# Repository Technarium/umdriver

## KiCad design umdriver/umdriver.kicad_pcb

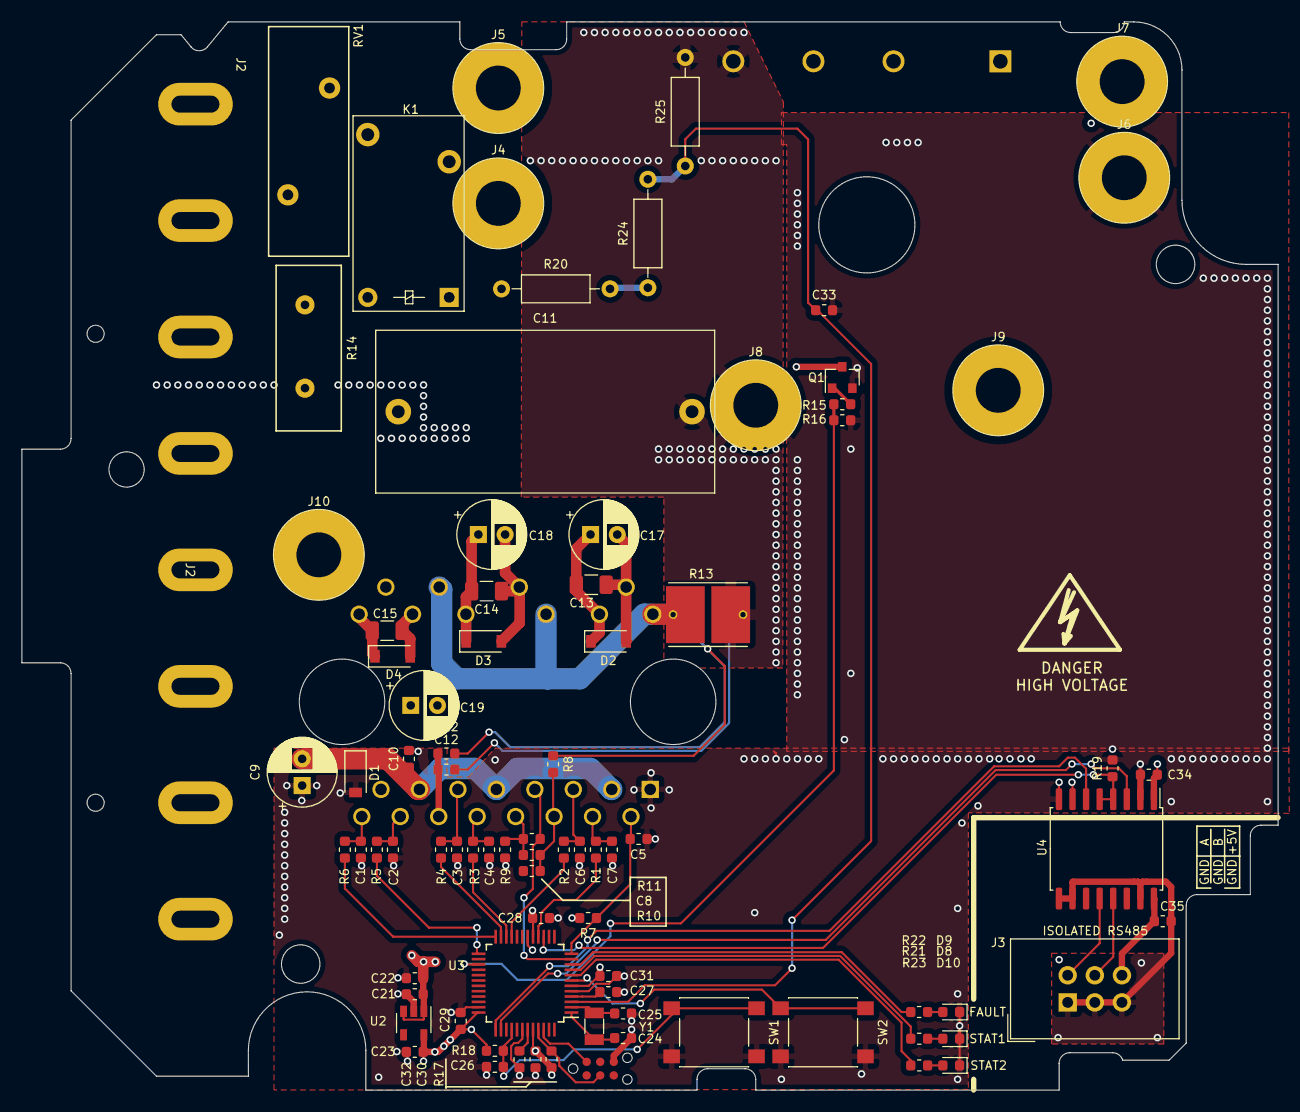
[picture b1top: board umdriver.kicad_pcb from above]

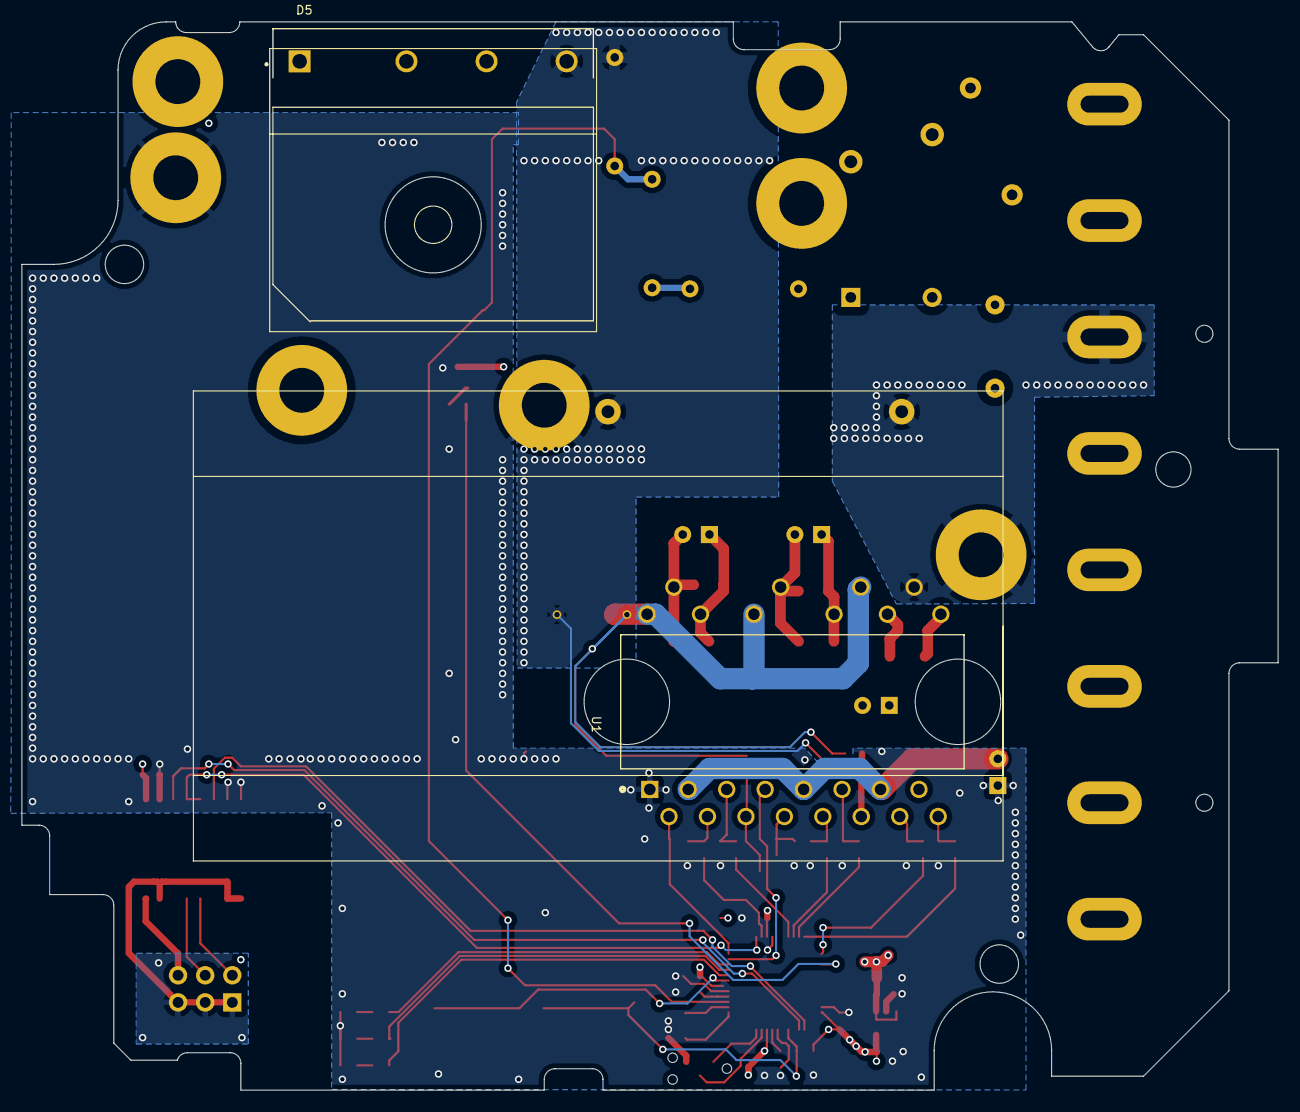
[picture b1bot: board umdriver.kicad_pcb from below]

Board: 4 copper layers, 117.6 x 100.0 mm, 87 parts (2 on the bottom side), 57 nets.

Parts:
C1, C2, C3, C4, C5, C6, C7, C12: 1n; C_0603_1608Metric
C8: 100p; C_0603_1608Metric
C9, C17, C18, C19: 10u; CP_Radial_D6.3mm_P2.50mm
C10: 0.1u; C_0603_1608Metric
C11: 7u 650V; C_Rect_L31.5mm_W15.0mm_P27.50mm_MKS4
C13, C14, C15: 2.2u; C_1206_3216Metric
C21, C22, C23: 4.7u; C_0603_1608Metric
C24, C25: 22p; C_0603_1608Metric
C26, C27, C28, C29, C30, C31, C32, C33, C34, C35: 1u; C_0603_1608Metric
D1, D2, D3, D4: 20V; D_SOD-123
D5: D_Bridge_+AA-; DIOB_GSIB2560-E3-45
D8, D9, D10: LED; LED_0603_1608Metric
J1: SWD; TC2030-MCP-NL
J2: Conn_01x08; TB-YAG-8P
J3: Isolated rs485; IDC-Header_2x03_Pitch2.54mm_Straight
J4, J5, J6, J7, J8, J9, J10: Conn_01x01; WURTH-7466003
K1: SPST; Relay_SPST
Q1: Q_NMOS_GDS; SOT-23
R1, R2, R3, R4, R5, R6: 100; R_0603_1608Metric
R7, R12, R17, R18, R21, R22, R23: 1k; R_0603_1608Metric
R8, R9: 1.0k; R_0603_1608Metric
R10, R11: 1.9k; R_0603_1608Metric
R13: 0.090 7W; RESC_WSHM2818R0150FEA
R14: 1k; RV_Disc_D15.5_W6.1_P7.5
R15, R16: R; R_0603_1608Metric
R19: 1M; R_0603_1608Metric
R20, R24: 100k; R_Axial_DIN0207_L6.3mm_D2.5mm_P10.16mm_Horizontal
R25: 1.8k; R_Axial_DIN0207_L6.3mm_D2.5mm_P10.16mm_Horizontal
RV1: Varistor; RV_Disc_D21.5_W7.5_P10
SW1: SW_Reset; SW_Push_1P1T_NO_6x6mm_H9.5mm
SW2: SW_Test; SW_Push_1P1T_NO_6x6mm_H9.5mm
SYM1: SYM_Flash_Small; Symbol_HighVoltage_Type2_Silkscreen_VerySmall
U1: STGIPQ8C60T; ST_STGIPQ8C60T-HZ
U2: NCP718; SOT-23-5
U3: ATSAMD21G18A-AUT; TQFP-48_7x7mm_P0.5mm
U4: ISO3088DW; SOIC-16W_7.5x10.3mm_P1.27mm
Y1: 32.768; Crystal_SMD_3215-2pin_3.2x1.5mm

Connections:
+3V3: C23.1, C28.1, C29.1, C30.1, C31.1, C34.1, R7.2, R17.1, R18.1, U2.5, U3.6, U3.17, U3.36, U3.44, U4.1
+15V: C9.2, C10.1, C21.1, C22.1, D1.1, J7.1, K1.A2, U1.3, U1.9, U1.13, U2.1, U2.3
/DC_BUS_MON: C33.1, R24.2, R25.1, U3.3
/HINU: R5.1, U3.25
/HINUF: C2.1, R5.2, U1.14
/HINV: R3.1, U3.22
/HINVF: C4.1, R3.2, U1.10
/HINW: R1.1, U3.16
/HINWF: C7.1, R1.2, U1.4
/INRUSH_BYPASS: R15.2, R16.1, U3.27
/ISENSE: R11.2, U1.7, U3.11
/LINE_L: J2.2, J4.1, K1.11, R14.1, RV1.1
/LINE_N: D5.AC2, J2.1, J5.1, RV1.2
/LINU: R6.1, U3.24
/LINUF: C1.1, R6.2, U1.16
/LINV: R4.1, U3.23
/LINVF: C3.1, R4.2, U1.11
/LINW: R2.1, U3.21
/LINWF: C6.1, R2.2, U1.5
/Microcontroller/ISO_A: J3.2, U4.12
/Microcontroller/ISO_B: J3.4, U4.13
/Microcontroller/ISO_GND: C35.2, J3.1, J3.3, J3.5, U4.9, U4.10, U4.15
/Microcontroller/ISO_VCC: C35.1, J3.6, U4.16
/Microcontroller/LED1: R21.1, U3.9
/Microcontroller/LED2: R22.1, U3.10
/Microcontroller/LED3: R23.1, U3.8
/Microcontroller/MCU_AREF: C27.1, U3.4
/Microcontroller/RX: U3.38, U4.3
/Microcontroller/SWD_CLK: J1.3, R17.2, U3.45
/Microcontroller/SWD_IO: J1.2, U3.46
/Microcontroller/TX: U3.37, U4.6
/Microcontroller/~MCU_RST: C26.1, R18.2, SW1.2, U3.40
/Microcontroller/~RS485_RE: R19.1, U3.15, U4.4, U4.5
/NTC: C5.1, R7.1, U1.2, U3.12
/UOUT: C15.1, C19.2, D4.2, J2.4, U1.19
/VBOOTU: C15.2, C19.1, D4.1, U1.17
/VBOOTV: C14.2, C18.1, D3.1, U1.21
/VBOOTW: C13.2, C17.1, D2.1, U1.24
/VOUT: C14.1, C18.2, D3.2, J2.5, U1.22
/VSHUNT: R8.1, R12.2, R13.1, U1.20, U1.23, U1.26
/WOUT: C13.1, C17.2, D2.2, J2.6, U1.25
GND: C1.2, C2.2, C3.2, C4.2, C5.2, C6.2, C7.2, C9.1, C10.2, C11.2, C12.2, C21.2, C22.2, C23.2, C24.2, C25.2, C26.2, C27.2, C28.2, C29.2, C30.2, C31.2, C32.2, C33.2, C34.2, D1.2, D5.-, D8.1, D9.1, D10.1, J1.6, J6.1, J8.1, Q1.2, R9.1, R13.2, R16.2, R19.2, R25.2, SW1.1, SW2.1, U1.1, U2.2, U3.5, U3.18, U3.35, U3.42, U4.2, U4.7, U4.8
unnamed: C8.1, R8.2, R10.1, U1.6
unnamed: C8.2, R9.2, R11.1, U1.8
unnamed: C12.1, R12.1, U1.12
unnamed: C24.1, U3.1, Y1.2
unnamed: C25.1, U3.2, Y1.1
unnamed: C32.1, U3.43
unnamed: D5.AC1, K1.14, R14.2
unnamed: D8.2, R21.2
unnamed: D9.2, R22.2
unnamed: D10.2, R23.2
unnamed: K1.A1, Q1.3
unnamed: Q1.1, R15.1
unnamed: R20.2, R24.1
unnamed: SW2.2, U3.7
VBUS: C11.1, D5.+, J2.3, J9.1, J10.1, R20.1, U1.18

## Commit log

2020-02-13 Add a power supply. Not clear yet if it is sufficient current-vise
2020-02-18 Source the most of the components, update footprints
2020-02-23 add yaskawa case pcb drawings
2020-02-23 update PCB drawings
2020-02-25 Source bridge rectifier, import board shape, start placing and routing on the real shape
2020-02-25 Try routing the MCU part
2020-02-25 Route more MCU tracks
2020-02-28 Main board routing complete
2020-02-29 Add DC BUS board connectors, move stuff a bit, fix VOUT zone so it's capable to thruput some current
